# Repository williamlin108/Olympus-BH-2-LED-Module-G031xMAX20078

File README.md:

# USB-C PD High-CRI LED Driver for Olympus BH-2 BHTU Microscopes

A compact, USB-C powered constant-current LED driver built around the Maxim **MAX20078** synchronous buck controller and an **STM32G031** microcontroller. It drives a high-CRI **Nichia 519A** emitter at up to **5 A**, with user-configurable control, saved settings, safety limits, and heavy input protection.

Built specifically to replace and upgrade the **discontinued halogen bulb assembly of Olympus BH2 lab microscopes**. It drops into the original lamp housing and swaps the hot, short-lived halogen bulb for a cool, efficient, high-CRI LED, while adding USB-C power, presets, and precise brightness control.

## Photos

| Driver board and LED module | Running on USB-C PD |
|---|---|
|  |  |

## Features

- **USB-C Power Delivery input:** Infineon **CYPD3177** (EZ-PD BCR) sink controller negotiates a higher PD voltage from any USB-C charger
- **5 A constant-current buck:** MAX20078 synchronous buck LED controller with a BSG0811ND dual N-MOSFET power stage
- **High-CRI output:** tuned for the Nichia 519A for accurate color rendering
- **Smart dimming:** STM32 firmware handles smooth ramping, gamma-corrected brightness, off mode, and fault latching
- **User extensible:** open firmware so users can add their own macros, saved settings, and custom safety limits
- **Hardware-debounced buttons:** SR-latch debounce using SPDT switches and an SN74AC00 NAND gate
- **Fault handling:** the MAX20078 fault output is monitored and handled in firmware
- **Protection:** TVS clamping, fusing, EMI filtering, and gate/transient clamps
- **Custom CNC Nichia 519 Holder** Custom designed CNC 6061 Aluminum heatsink and male socket part that slides into the BHTU's rear illumination port with O-rings to prevent wear and ensure a tight friction fit.

## System Overview

```
USB-C ──► Fuse ──► TVS2200 ──► BNX025 EMI filter ──► CYPD3177 PD sink ──► VBUS load switch ──► VIN
                                                                                               │
                              ┌────────────────────────────────────────────────────────────────┤
                              ▼                                                                ▼
                    TPS7E82 LDO (3.3 V)                     MAX20078 buck ──► BSG0811ND ──► 4.7 µH ──► Nichia 519A
                              │                               ▲     │   ▲                                     │
                              ▼                               │     │   └── CSP/CSN current sense (shunt) ◄───┘
                     STM32G031 ─────── DIM (PWM) ─────────────┘     │
                        ▲    ◄─────────────────── FLT ──────────────┘
                        │
         SW1/SW2 (SPDT) ──► SN74AC00 SR-latch debounce
```

## Hardware

| Block | Part | Role |
|---|---|---|
| PD sink | Infineon CYPD3177-24LQ | Negotiates USB-C PD voltage; drives the VBUS load switch |
| Input protection | TI TVS2200DRV | Flat-clamp TVS on VBUS |
| EMI filter | Murata BNX025 | Input noise suppression |
| Fuse | F1 | Input overcurrent protection |
| LED controller | MAX20078ATE+T | Synchronous buck, constant-current LED regulation |
| Power stage | BSG0811ND dual N-MOSFET | High-side / low-side switches |
| Inductor | 4.7 µH | Buck output inductor |
| Current sense | 0.1 Ω shunt (Kelvin-routed CSP/CSN) | LED current feedback |
| MCU | STM32G031J6 | UI, settings, dimming, fault handling |
| LDO | TPS7E8233-Q1 | 3.3 V logic supply |
| Buttons | 2× Omron D2F-01F (SPDT) | User input |
| Debounce | SN74AC00 quad NAND | Cross-coupled SR latches |
| Emitter | Nichia 519A | High-CRI LED |

### Protection

- **Fuse** on the USB-C VBUS input
- **TVS2200** flat-clamp surge protection against hot-plug and ESD transients
- **Murata BNX025** EMI filter on the input to keep switching noise off the cable
- **Zener gate clamp** (MMSZ4702) on the VBUS load switch
- **Schottky diodes** (B340A, B5819W) for bootstrap and transient paths
- **Bulk and decoupling capacitance** (22 µF ceramics) on input and output
- **Dedicated current-sense net class** for accurate, low-noise regulation
- **Firmware limits** on maximum current and shutdown on fault

### Hardware Debounce

Each button is an SPDT switch wired to a cross-coupled NAND **SR latch** in the SN74AC00. The latch changes state on the first contact and ignores bounce, so the STM32 sees one clean edge on `ENCA` / `ENCB` per press without software debounce delays.

### Connectors & Test Points

| Ref | Description |
|---|---|
| J1 | USB-C power input (PD) |
| J2 | LED output (LED+, LED−) |
| J3 | TC2030 SWD programming / debug |
| TP1 | VDC |
| TP2, TP4 | GND |
| TP3 | GPIO (debug) |

## Firmware

Written in bare-metal C using the STM32 libraries (no RTOS). The STM32G031 provides:

- **PWM dimming:** TIM3 drives the MAX20078 `DIM` input with 32,000 steps of resolution
- **Smooth ramp:** hold up/down to sweep brightness over 3 s; level is computed from elapsed time so the sweep is exact
- **Perceptual curve:** square-law gamma so brightness changes look even across the range
- **Off mode:** hold down past minimum to turn fully off; press up to wake at minimum
- **Minimum on-time floor:** DIM pulses never drop below the width the current loop needs to settle
- **Fault handling:** `FLT` falling edge is confirmed by re-read, then latched; output is held at minimum (not released, which would let the DIM pull-up drive full brightness). Shutdown and wake-up `FLT` pulses are masked
- **Status LED:** blinks while adjusting, solid on a latched fault (clears on power cycle)
- **Software debounce** on top of the hardware latches, to reject switching-noise glitches

### Extending the Firmware

The firmware is meant to be customized. Users can add their own features, for example:

- **Macros / presets:** e.g. a double-press to jump to a saved brightness
- **Saved settings:** store the last level in flash and restore it on power-up
- **Custom safety limits:** cap the maximum duty for a given emitter or optics setup

| Pin | Function |
|---|---|
| PB0 | TIM3_CH3 PWM → MAX20078 DIM |
| PA12 | MAX20078 FLT (active low) |
| PA13 | Up button |
| PA15 | Down button |
| PB7 | Status LED (open drain) |

## Repository Layout

```
PCBfiles/
  CombinedLEDdriverMAX278.kicad_pro   KiCad project
  CombinedLEDdriverMAX278.kicad_sch   Top-level schematic (buck, MCU, LDO)
  usbc_input.kicad_sch                USB-C PD sink, fuse, TVS, EMI filter
  switches.kicad_sch                  Buttons and SR-latch debounce
Firmware/                             STM32G031 bare-metal C firmware
images/                               Photos used in this README
```

## Getting Started

1. Flash the STM32 over SWD using a TC2030 cable.
2. Connect the Nichia 519A to J2, observing polarity.
3. Plug in a USB-C PD charger capable of the required power.
4. Hold the up/down buttons to ramp brightness; hold down past minimum to turn off.

> Heat sink the emitter properly before running at full current.

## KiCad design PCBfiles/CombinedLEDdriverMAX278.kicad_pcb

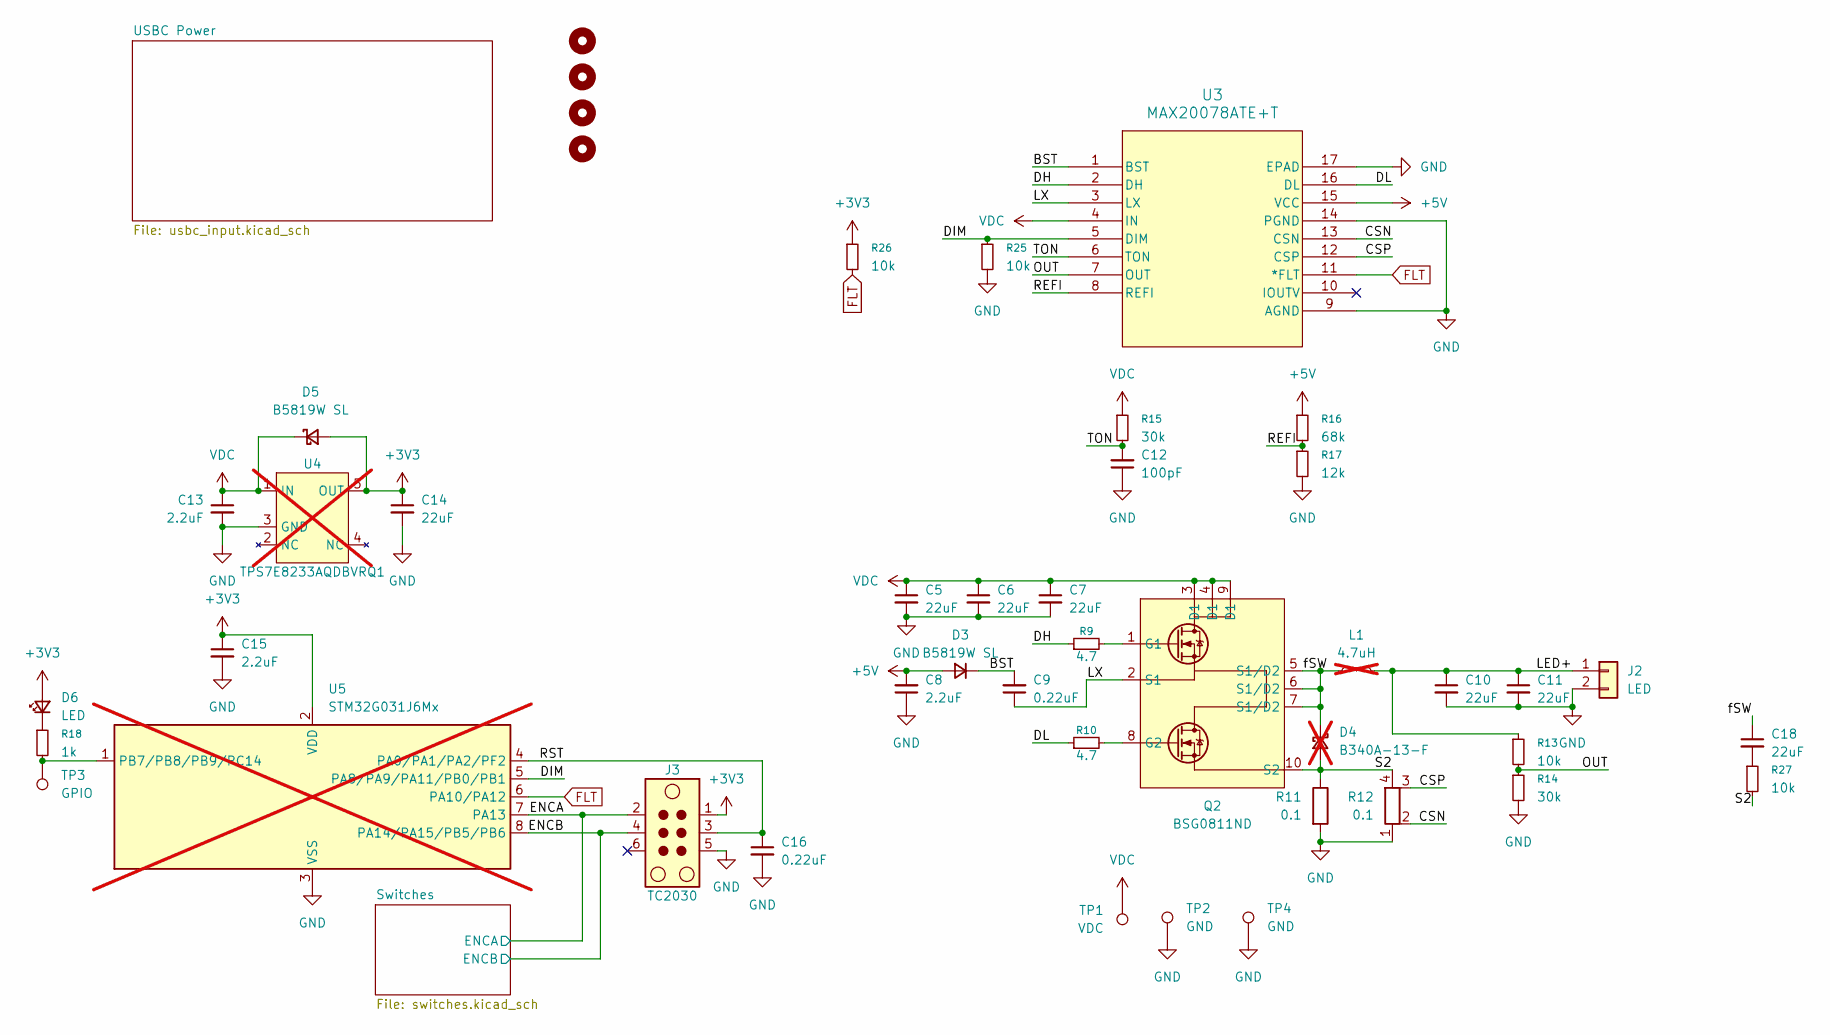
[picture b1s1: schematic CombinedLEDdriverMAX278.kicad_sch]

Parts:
C5, C6, C7, C10, C11, C14: 22uF; C_0805_2012Metric
C8, C13, C15: 2.2uF; C_0603_1608Metric
C9, C16: 0.22uF; C_0603_1608Metric
C12: 100pF; C_0603_1608Metric
C18: 22uF; C_0603_1608Metric_Pad1.08x0.95mm_HandSolder
D3, D5: B5819W SL; D_SOD-123
D4: B340A-13-F; D_SMA; not fitted
D6: LED; LED_0805_2012Metric
H1, H2, H3, H4: MountingHole; MountingHole_2.7mm_M2.5
J2: LED; Molex_SPOX_5267-02A_1x02_P2.50mm_Vertical
J3: TC2030; Tag-Connect_TC2030-IDC-NL_2x03_P1.27mm_Vertical
L1: 4.7uH; L_Vishay_IHLP-4040; not fitted
Q2: BSG0811ND; Infineon_PG-TISON-8-4
R9, R10: 4.7; R_0603_1608Metric
R11, R12: 0.1; R_0805_2012Metric
R13, R25, R26: 10k; R_0603_1608Metric
R14, R15: 30k; R_0603_1608Metric
R16: 68k; R_0603_1608Metric
R17: 12k; R_0603_1608Metric
R18: 1k; R_0603_1608Metric
R27: 10k; R_0603_1608Metric_Pad0.98x0.95mm_HandSolder
TP1: VDC; TestPoint_Pad_D1.0mm
TP2: GND; TestPoint_Pad_D1.0mm
TP3: GPIO; TestPoint_Pad_D1.0mm
TP4: GND; TestPoint_Keystone_5015_Micro_Mini
U3: MAX20078ATE+T; MAX20078_QFN
U4: TPS7E8233AQDBVRQ1; SOT-23-5; not fitted
U5: STM32G031J6Mx; SOIC-8_3.9x4.9mm_P1.27mm; not fitted

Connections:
+3V3: C14.1, C15.1, D5.2 (A), D6.2 (A), J3.1, R26.1, U4.5 (OUT), U5.2 (VDD); also elsewhere on the board
+5V: C8.2, D3.2 (A), R16.1, U3.15 (VCC)
/BST: C9.2, D3.1 (K), U3.1 (BST)
/CSN: R12.2, U3.13 (CSN)
/CSP: R12.3, U3.12 (CSP)
/DH: R9.1, U3.2 (DH)
/DIM: R25.1, U3.5 (DIM), U5.5 (PA8/PA9/PA11/PB0/PB1)
/DL: R10.1, U3.16 (DL)
/ENCA: J3.2, U5.7 (PA13); also elsewhere on the board
/ENCB: J3.4, U5.8 (PA14/PA15/PB5/PB6); also elsewhere on the board
/LED+: C10.1, C11.1, J2.1, L1.2, R13.1
/LX: C9.1, Q2.2 (S1), U3.3 (LX)
/OUT: R13.2, R14.1, U3.7 (OUT)
/REFI: R16.2, R17.1, U3.8 (REFI)
/RST: C16.1, J3.3, U5.4 (PA0/PA1/PA2/PF2)
/S2: D4.2 (A), Q2.10 (S2), R11.1, R12.4, R27.2
/TON: C12.2, R15.2, U3.6 (TON)
/fSW: C18.1, D4.1 (K), L1.1, Q2.5 (S1/D2), Q2.6 (S1/D2), Q2.7 (S1/D2)
FLT: R26.2, U3.11 (*FLT), U5.6 (PA10/PA12)
GND: C5.2, C6.2, C7.2, C8.1, C10.2, C11.2, C12.1, C13.2, C14.2, C15.2, C16.2, J2.2, J3.5, R11.2, R12.1, R14.2, R17.2, R25.2, TP2.1, TP4.1, U3.9 (AGND), U3.14 (PGND), U3.17 (EPAD), U4.3 (GND), U5.3 (VSS); also elsewhere on the board
unnamed: C18.2, R27.1
unnamed: D6.1 (K), R18.1
unnamed: Q2.1 (G1), R9.2
unnamed: Q2.8 (G2), R10.2
unnamed: R18.2, TP3.1, U5.1 (PB7/PB8/PB9/PC14)
VDC: C5.1, C6.1, C7.1, C13.1, D5.1 (K), Q2.3 (D1), Q2.4 (D1), Q2.9 (D1), R15.1, TP1.1, U3.4 (IN), U4.1 (IN); also elsewhere on the board

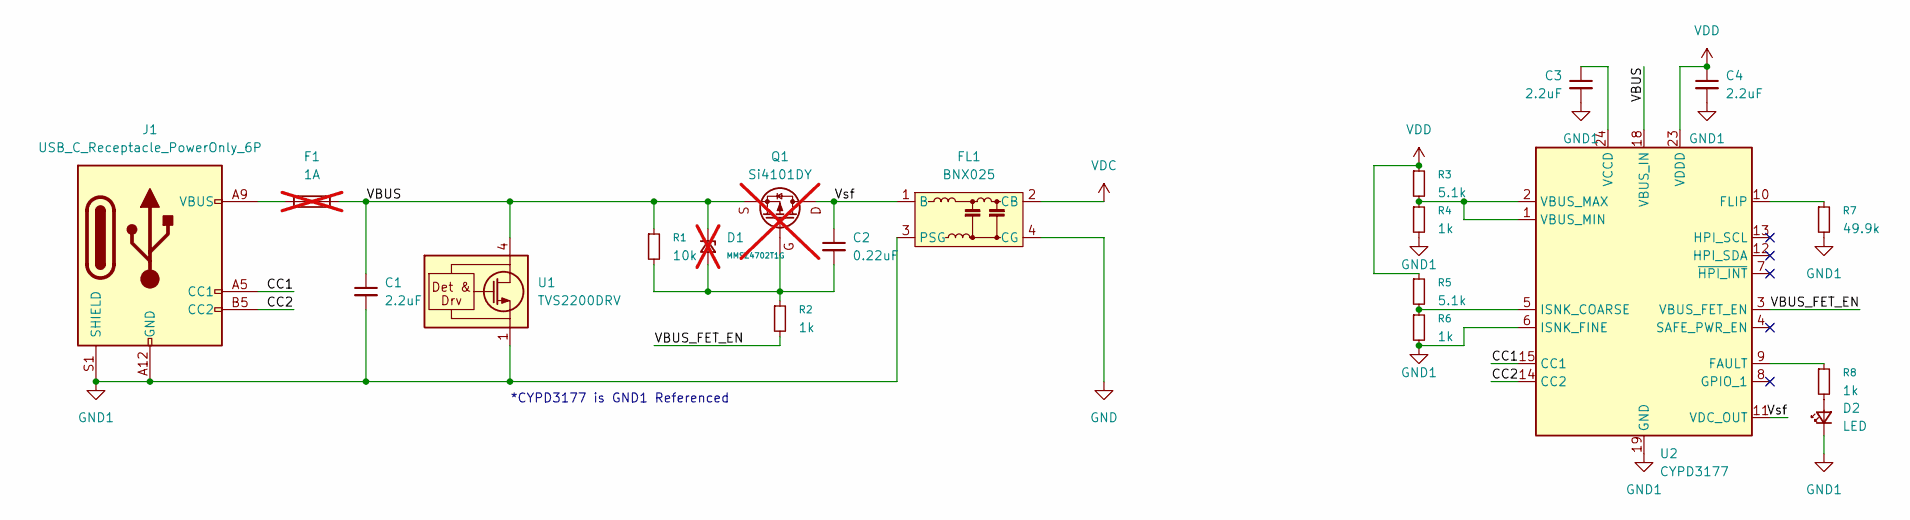
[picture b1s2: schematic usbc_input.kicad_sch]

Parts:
C1, C3, C4: 2.2uF; C_0603_1608Metric
C2: 0.22uF; C_0603_1608Metric
D1: MMSZ4702T1G; D_SOD-123; not fitted
D2: LED; LED_0805_2012Metric
F1: 1A; Fuse_1206_3216Metric_Pad1.42x1.75mm_HandSolder; not fitted
FL1: BNX025; Filter_Murata_BNX025
J1: USB_C_Receptacle_PowerOnly_6P; USB_C_Receptacle_GCT_USB4125-xx-x_6P_TopMnt_Horizontal
Q1: Si4101DY; SOIC-8_3.9x4.9mm_P1.27mm; not fitted
R1: 10k; R_0603_1608Metric
R2, R4, R6, R8: 1k; R_0603_1608Metric
R3, R5: 5.1k; R_0603_1608Metric
R7: 49.9k; R_0603_1608Metric
U1: TVS2200DRV; WSON-6-1EP_2x2mm_P0.65mm_EP1x1.6mm
U2: CYPD3177; QFN-24-1EP_4x4mm_P0.5mm_EP2.75x2.75mm

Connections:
/USBC Power/CC1: J1.A5 (CC1), U2.15 (CC1)
/USBC Power/CC2: J1.B5 (CC2), U2.14 (CC2)
/USBC Power/VBUS: C1.1, D1.1 (K), F1.2, Q1.1 (S), Q1.2 (S), Q1.3 (S), R1.1, U1.4 (IN), U1.5 (IN), U1.6 (IN), U2.18 (VBUS_IN)
/USBC Power/VBUS_FET_EN: R2.2, U2.3 (VBUS_FET_EN)
/USBC Power/Vsf: C2.1, FL1.1 (B), Q1.5 (D), Q1.6 (D), Q1.7 (D), Q1.8 (D), U2.11 (VDC_OUT)
GND: FL1.4 (CG); also elsewhere on the board
GND1: C1.2, C3.2, C4.2, D2.1 (K), FL1.3 (PSG), J1.A12 (GND), J1.B12 (GND), J1.S1 (SHIELD), R4.2, R6.2, R7.2, U1.1 (GND), U1.2 (GND), U1.3 (GND), U1.7 (GND), U2.6 (ISNK_FINE), U2.19 (GND), U2.22 (GND), U2.25 (GND)
unnamed: C2.2, D1.2 (A), Q1.4 (G), R1.2, R2.1
unnamed: D2.2 (A), R8.2
unnamed: F1.1, J1.A9 (VBUS), J1.B9 (VBUS)
unnamed: R8.1, U2.9 (FAULT)
unnamed: R7.1, U2.10 (FLIP)
unnamed: R5.2, R6.1, U2.5 (ISNK_COARSE)
unnamed: R3.2, R4.1, U2.1 (VBUS_MIN), U2.2 (VBUS_MAX)
unnamed: C3.1, U2.24 (VCCD)
VDC: FL1.2 (CB); also elsewhere on the board
VDD: C4.1, R3.1, R5.1, U2.23 (VDDD)

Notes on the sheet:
*CYPD3177 is GND1 Referenced

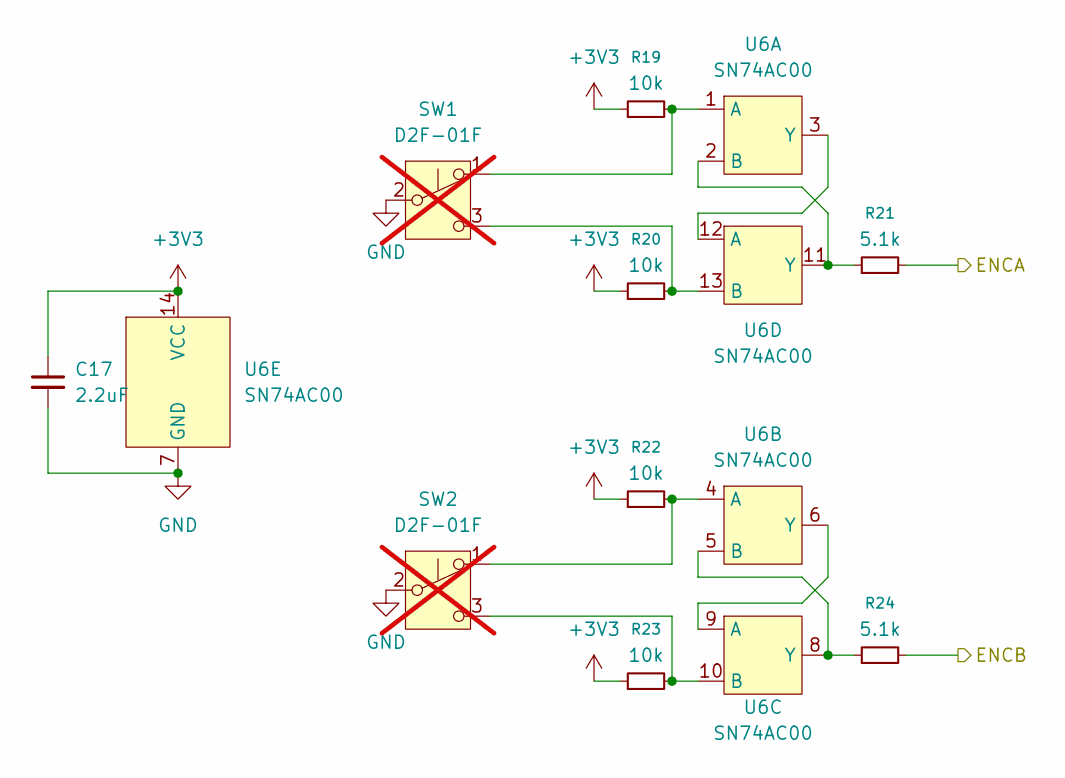
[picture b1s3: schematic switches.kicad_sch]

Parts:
C17: 2.2uF; C_0603_1608Metric
R19, R20, R22, R23: 10k; R_0603_1608Metric
R21, R24: 5.1k; R_0603_1608Metric
SW1, SW2: D2F-01F; not fitted
U6: SN74AC00; TSSOP-14_4.4x5mm_P0.65mm

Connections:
+3V3: C17.1, R19.1, R20.1, R22.1, R23.1, U6.14 (VCC); also elsewhere on the board
/ENCA: R21.2; also elsewhere on the board
/ENCB: R24.2; also elsewhere on the board
GND: C17.2, SW1.2 (B), SW2.2 (B), U6.7 (GND); also elsewhere on the board
unnamed: R19.2, SW1.1 (A), U6.1 (A)
unnamed: R20.2, SW1.3 (C), U6.13 (B)
unnamed: R22.2, SW2.1 (A), U6.4 (A)
unnamed: R23.2, SW2.3 (C), U6.10 (B)
unnamed: R21.1, U6.2 (B), U6.11 (Y)
unnamed: U6.3 (Y), U6.12 (A)
unnamed: R24.1, U6.5 (B), U6.8 (Y)
unnamed: U6.6 (Y), U6.9 (A)

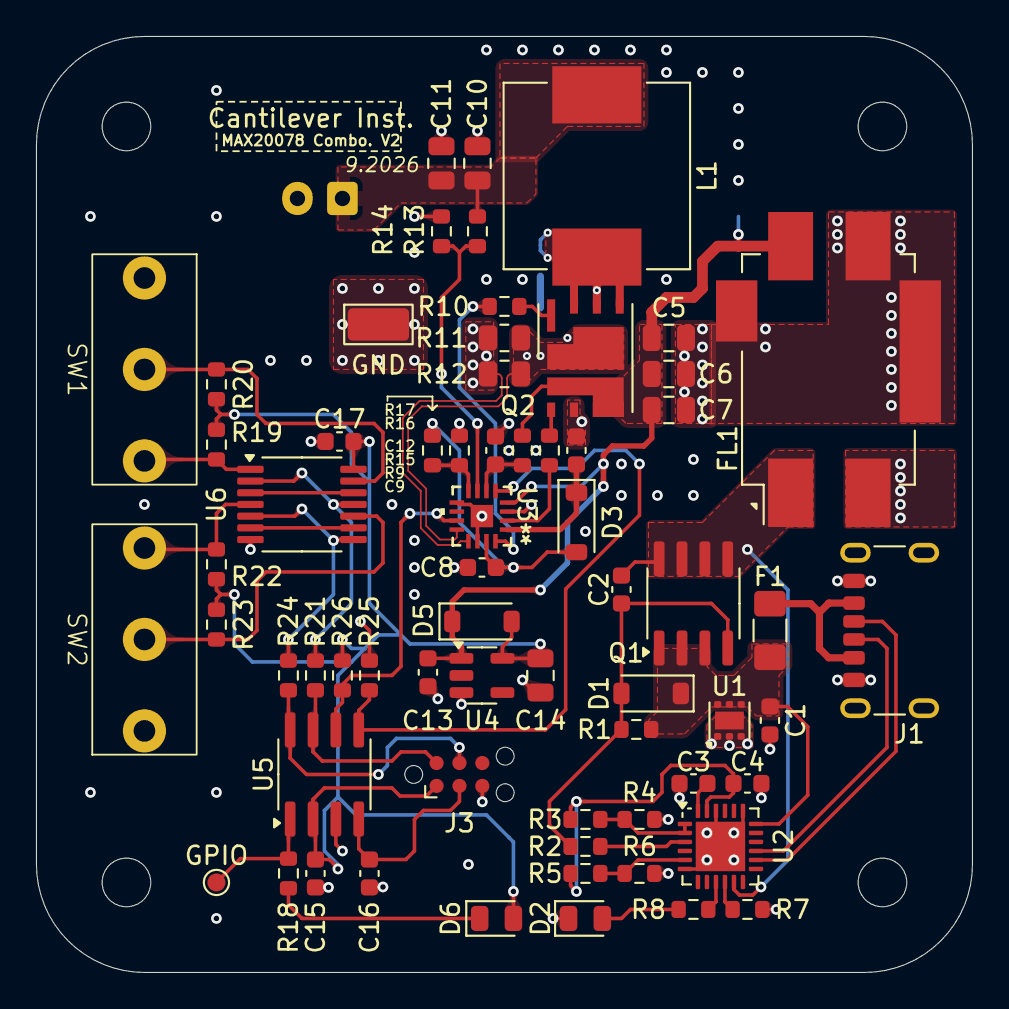
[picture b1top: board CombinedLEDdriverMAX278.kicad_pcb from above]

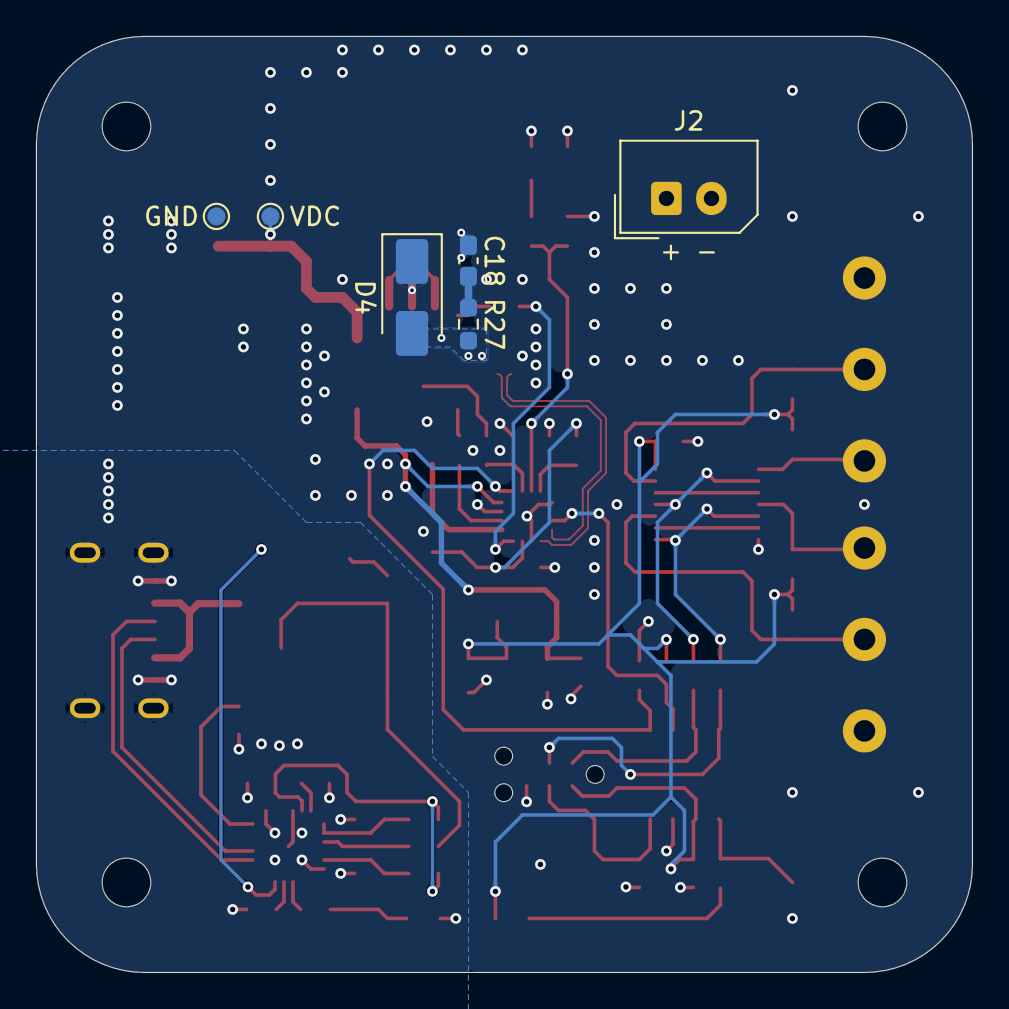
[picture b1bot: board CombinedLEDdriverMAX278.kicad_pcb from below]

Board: 4 copper layers, 52.0 x 52.0 mm, 75 parts (6 on the bottom side), 49 nets.

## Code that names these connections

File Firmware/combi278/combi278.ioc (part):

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Mcu.Name=STM32G031J(4-6)Mx
Mcu.Package=SO8N
Mcu.UserName=STM32G031J6Mx
PA12\ [PA10].GPIOParameters=GPIO_PuPd,GPIO_Label,GPIO_ModeDefaultEXTI
PA12\ [PA10].GPIO_Label=FLT
PA12\ [PA10].GPIO_ModeDefaultEXTI=GPIO_MODE_IT_FALLING
PA12\ [PA10].GPIO_PuPd=GPIO_PULLUP
PA12\ [PA10].Signal=GPXTI12
PA13.GPIOParameters=GPIO_PuPd,GPIO_Label
PA13.GPIO_Label=INCU
PA13.GPIO_PuPd=GPIO_PULLDOWN
PA13.Signal=GPIO_Input
PA14-BOOT0__PA15__PB5__PB6.StandardMode=true
PA15.GPIOParameters=GPIO_PuPd,GPIO_Label
PA15.GPIO_Label=INCD
PA15.GPIO_PuPd=GPIO_PULLDOWN
PA15.Signal=GPIO_Input
PB0.GPIOParameters=GPIO_Label
PB0.GPIO_Label=PWM
PB0.Signal=S_TIM3_CH3
PB0__PB1__PA8__PA11\ [PA9].StandardMode=true
PB7.GPIOParameters=PinState,GPIO_PuPd,GPIO_Label,GPIO_ModeDefaultOutputPP
PB7.GPIO_Label=LED
PB7.GPIO_ModeDefaultOutputPP=GPIO_MODE_OUTPUT_OD
PB7.GPIO_PuPd=GPIO_NOPULL
PB7.PinState=GPIO_PIN_SET
PB7.Signal=GPIO_Output
PC14-OSC32_IN\ (PC14)__PB7__PB8__PB9.StandardMode=true
PF2\ -\ NRST__PA0__PA1__PA2.StandardMode=true
RCC.HSE_VALUE=8000000
RCC.SYSCLKFreq_VALUE=64000000
RCC.SYSCLKSource=RCC_SYSCLKSOURCE_PLLCLK
board=custom
